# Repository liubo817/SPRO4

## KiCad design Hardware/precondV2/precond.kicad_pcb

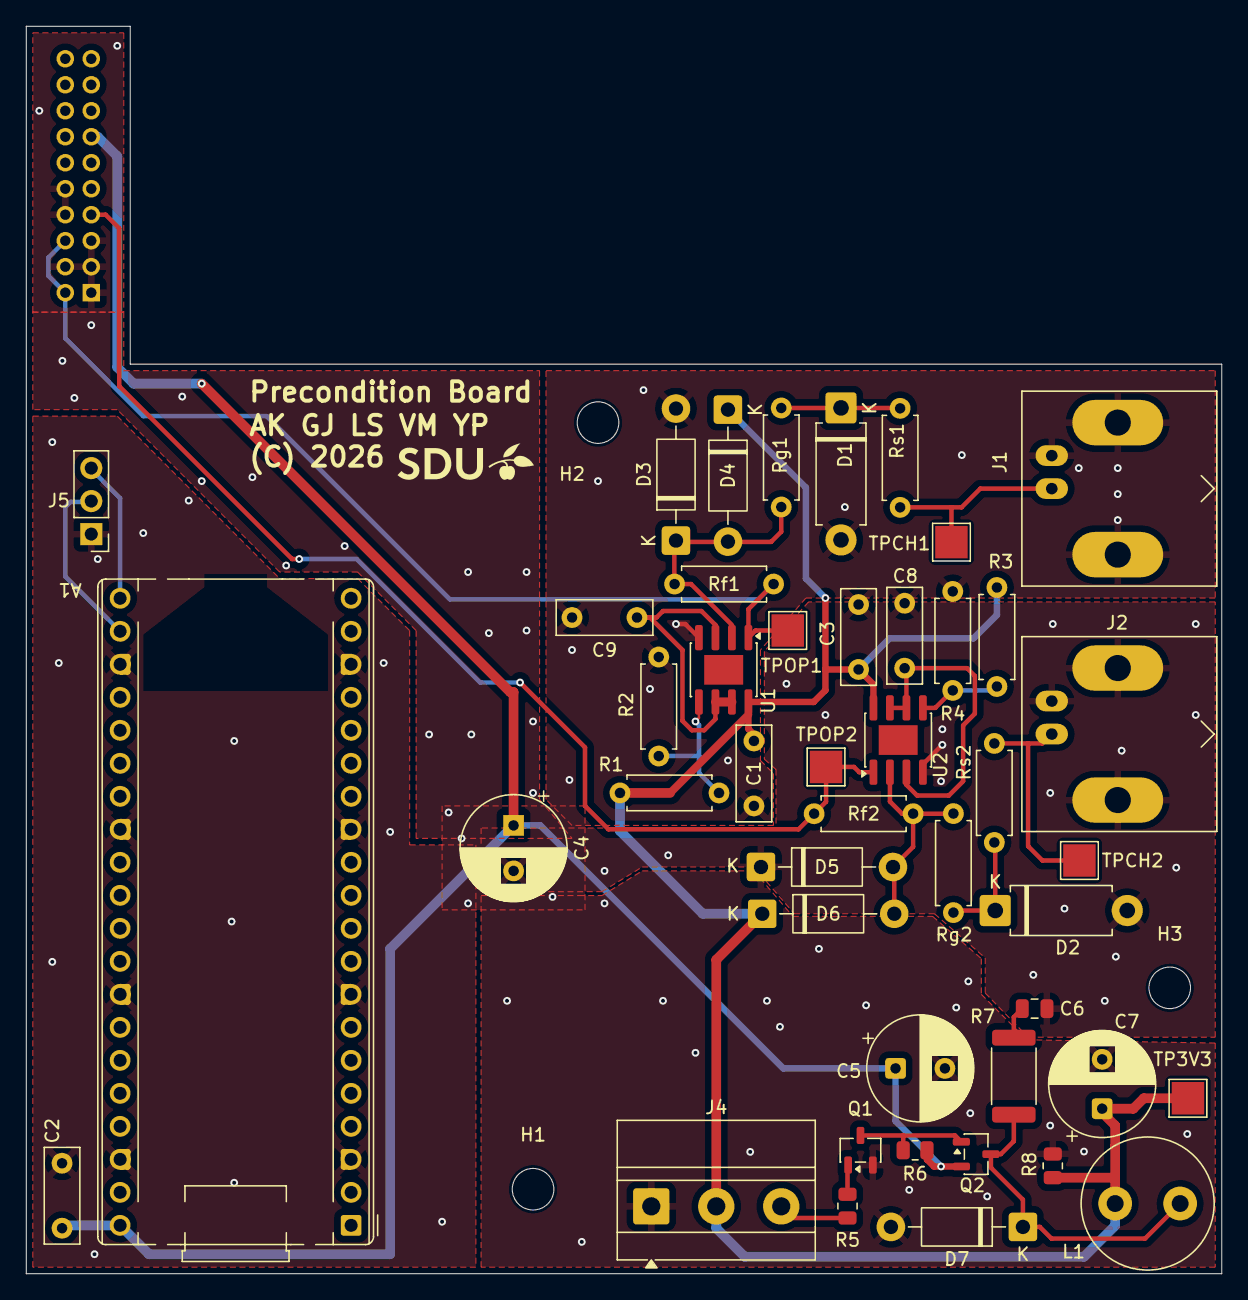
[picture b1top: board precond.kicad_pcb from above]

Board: 2 copper layers, 92.0 x 96.0 mm, 49 parts (1 on the bottom side), 22 nets.

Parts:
A1: RaspberryPi_Pico; RaspberryPi_Pico_Common_THT
C1, C2, C3, C8, C9: 100n; C_Rect_L7.2mm_W2.5mm_P5.00mm_FKS2_FKP2_MKS2_MKP2
C4: 47uF; CP_Radial_D8.0mm_P3.50mm
C5: 100uF; CP_Radial_D8.0mm_P3.80mm
C6: 1n; C_0805_2012Metric
C7: 220uF; CP_Radial_D8.0mm_P3.80mm
D1, D2: P6KE18CA; D_DO-15_P10.16mm_Horizontal
D3, D4, D5, D6, D7: 1N5819; D_DO-41_SOD81_P10.16mm_Horizontal
H1, H2, H3: MountingHole; MountingHole_3.2mm_M3
J1, J2: Conn_Coaxial; BNC_Amphenol_B6252HB-NPP3G-50_Horizontal
J3: XADC_header; PinSocket_2x10_P2.00mm_Vertical
J4: Screw_Terminal_01x03; TerminalBlock_MetzConnect_Type011_RT05503HBLC_1x03_P5.00mm_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
J5: UART_hdr; PinHeader_1x03_P2.54mm_Vertical
L1: 470uH; L_Radial_D10.0mm_P5.00mm_Fastron_07M
Q1: IRLML6344TRPBF; SOT-23-3
Q2: IRLML9301TRPBF; SOT-23-3
R1, R3: 56k; R_Axial_DIN0207_L6.3mm_D2.5mm_P7.62mm_Horizontal
R2, R4: 10k; R_Axial_DIN0207_L6.3mm_D2.5mm_P7.62mm_Horizontal
R5, R8: 1k; R_0805_2012Metric
R6: 100; R_0805_2012Metric
R7: 22; R_2512_6332Metric
Rf1, Rf2: 200k; R_Axial_DIN0207_L6.3mm_D2.5mm_P7.62mm_Horizontal
Rg1, Rg2: 200k; R_Axial_DIN0207_L6.3mm_D2.5mm_P7.62mm_Horizontal
Rs1, Rs2: 1k; R_Axial_DIN0207_L6.3mm_D2.5mm_P7.62mm_Horizontal
TP3V3: TestPoint; TestPoint_Pad_2.5x2.5mm
TPCH1, TPCH2: TestPoint; TestPoint_Pad_2.5x2.5mm
TPOP1, TPOP2: TestPoint; TestPoint_Pad_2.5x2.5mm
U1, U2: OPA2340; SOIC-8-1EP_3.9x4.9mm_P1.27mm_EP2.29x3mm

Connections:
+3.3V: C1.1, C3.1, C7.1, D4.1 (K), D6.1 (K), J4.2, L1.2, R1.1, R3.1, R8.1, TP3V3.1, U1.8 (V+), U2.8 (V+)
+5V: A1.40 (VBUS), C2.2, C4.1, C5.1, J3.13, Q2.2, R6.1
/Op0.5V_1: C9.1, U1.3 (+), U1.6 (-), U1.7
/Op0.5_2: C8.1, U2.3 (+), U2.6 (-), U2.7
/Op1_out: J3.2, J3.6, Rf1.2, TPOP1.1, U1.1
/Op2_out: J3.7, Rf2.2, TPOP2.1, U2.1
AGND: A1.3 (GND), A1.8 (GND), A1.13 (GND), A1.18 (GND), A1.23 (GND), A1.28 (GND), A1.33 (AGND), A1.38 (GND), C1.2, C2.1, C3.2, C4.2, C5.2, C6.2, C7.2, C8.2, C9.2, D1.2 (A2), D2.2 (A2), D3.2 (A), D5.1 (K), D7.2 (A), J1.2 (Ext), J2.2 (Ext), J3.1, J3.3, J3.4, J3.5, J3.8, J3.10, J4.1, J5.1, Q1.2, R2.2, R4.2, R8.2, U1.4 (V-), U2.4 (V-)
unnamed: A1.21 (GPIO16), J5.3
unnamed: A1.22 (GPIO17), J5.2
unnamed: C6.1, R7.2
unnamed: D1.1 (A1), Rg1.1, Rs1.2
unnamed: D2.1 (A1), Rg2.1, Rs2.2
unnamed: D3.1 (K), D4.2 (A), Rf1.1, Rg1.2, U1.2 (-)
unnamed: D5.2 (A), D6.2 (A), Rf2.1, Rg2.2, U2.2 (-)
unnamed: D7.1 (K), L1.1, Q2.3, R7.1
unnamed: J1.1 (In), Rs1.1, TPCH1.1
unnamed: J2.1 (In), Rs2.1, TPCH2.1
unnamed: J4.3, R5.2
unnamed: Q1.1, R5.1
unnamed: Q1.3, Q2.1, R6.2
unnamed: R1.2, R2.1, U1.5 (+)
unnamed: R3.2, R4.1, U2.5 (+)

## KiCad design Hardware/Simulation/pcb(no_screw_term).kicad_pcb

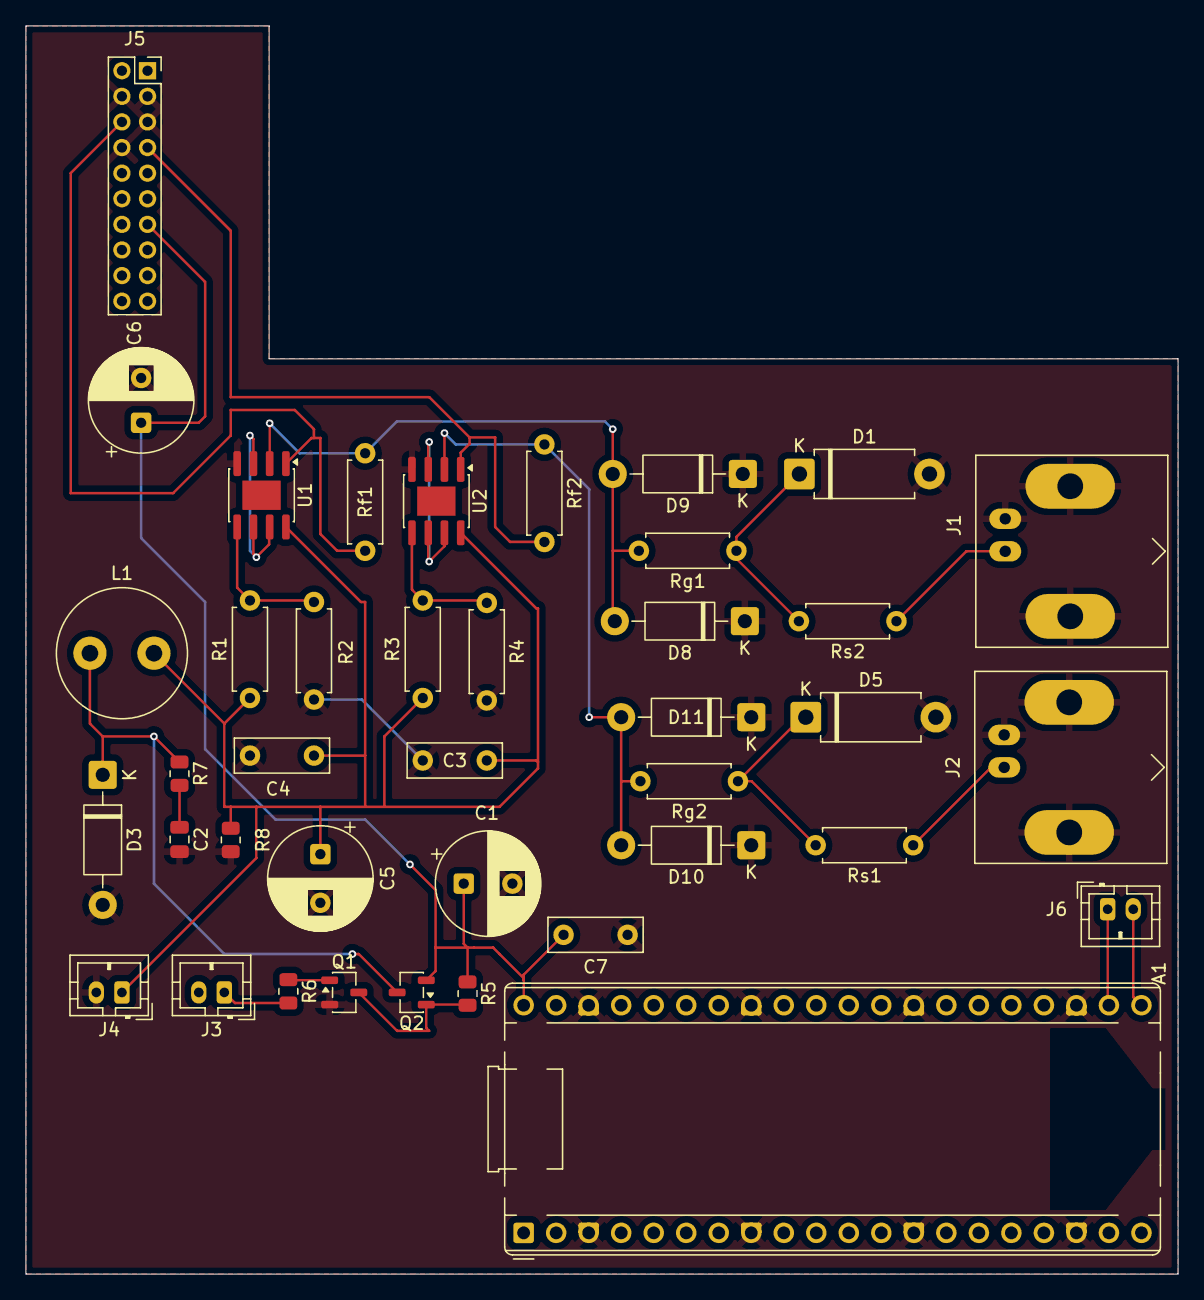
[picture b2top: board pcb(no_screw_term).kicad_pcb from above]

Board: 2 copper layers, 90.0 x 97.5 mm, 40 parts (0 on the bottom side), 22 nets.

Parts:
A1: RaspberryPi_Pico; RaspberryPi_Pico_Common_THT
C1: 100uF; CP_Radial_D8.0mm_P3.80mm
C2: 1n; C_0805_2012Metric
C3, C4, C7: 100n; C_Rect_L7.2mm_W2.5mm_P5.00mm_FKS2_FKP2_MKS2_MKP2
C5: 220uF; CP_Radial_D8.0mm_P3.80mm
C6: 47uF; CP_Radial_D8.0mm_P3.50mm
D1, D5: P6KE18CA; D_DO-15_P10.16mm_Horizontal
D3, D8, D9, D10, D11: 1N5819; D_DO-41_SOD81_P10.16mm_Horizontal
J1, J2: Conn_Coaxial; BNC_Amphenol_B6252HB-NPP3G-50_Horizontal
J3: Buck_logic_in; JST_PH_B2B-PH-K_1x02_P2.00mm_Vertical
J4: 3.3V_header; JST_PH_B2B-PH-K_1x02_P2.00mm_Vertical
J5: XADC_headder; PinSocket_2x10_P2.00mm_Vertical
J6: Pmod_to_UART; JST_PH_B2B-PH-K_1x02_P2.00mm_Vertical
L1: 470uH; L_Radial_D10.0mm_P5.00mm_Fastron_07M
Q1: IRLML6344TRPBF; SOT-23-3
Q2: IRLML9301TRPBF; SOT-23-3
R1, R3: 56k; R_Axial_DIN0207_L6.3mm_D2.5mm_P7.62mm_Horizontal
R2, R4: 10k; R_Axial_DIN0207_L6.3mm_D2.5mm_P7.62mm_Horizontal
R5: 100; R_0805_2012Metric
R6, R8: 1k; R_0805_2012Metric
R7: 22; R_0805_2012Metric
Rf1, Rf2: 200k; R_Axial_DIN0207_L6.3mm_D2.5mm_P7.62mm_Horizontal
Rg1, Rg2: 200k; R_Axial_DIN0207_L6.3mm_D2.5mm_P7.62mm_Horizontal
Rs1, Rs2: 1k; R_Axial_DIN0207_L6.3mm_D2.5mm_P7.62mm_Horizontal
U1, U2: OPA2340; SOIC-8-1EP_3.9x4.9mm_P1.27mm_EP2.29x3mm

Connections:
+3.3V: C3.1, C4.1, C5.1, J4.1, L1.2, R1.1, R3.1, R8.1, U1.8 (V+), U2.8 (V+)
+5V: A1.40 (VBUS), C1.1, C6.1, C7.2, J5.13, Q2.2, R5.1
/Op0.5V_1: U1.3 (+), U1.6 (-), U1.7
/Op0.5_2: U2.3 (+), U2.6 (-), U2.7
/Op1_out: J5.6, Rf1.2, U1.1
/Op2_out: J5.7, Rf2.2, U2.1
GND: A1.3 (GND), A1.8 (GND), A1.13 (GND), A1.18 (GND), A1.23 (GND), A1.28 (GND), A1.33 (AGND), A1.38 (GND), C1.2, C2.2, C3.2, C4.2, C5.2, C6.2, C7.1, D1.2 (A2), D3.2 (A), D5.2 (A2), D8.1 (K), D9.1 (K), D10.1 (K), D11.1 (K), J1.2 (Ext), J2.2 (Ext), J4.2, J5.3, J5.4, J5.5, J5.8, Q1.2, R2.2, R4.2, R8.2, U1.4 (V-), U2.4 (V-)
unnamed: A1.21 (GPIO16), J6.2
unnamed: A1.22 (GPIO17), J6.1
unnamed: C2.1, R7.2
unnamed: D1.1 (A1), Rg1.1, Rs2.2
unnamed: D3.1 (K), L1.1, Q2.3, R7.1
unnamed: D5.1 (A1), Rg2.1, Rs1.2
unnamed: D8.2 (A), D9.2 (A), Rf1.1, Rg1.2, U1.2 (-)
unnamed: D10.2 (A), D11.2 (A), Rf2.1, Rg2.2, U2.2 (-)
unnamed: J1.1 (In), Rs2.1
unnamed: J2.1 (In), Rs1.1
unnamed: J3.1, R6.2
unnamed: Q1.1, R6.1
unnamed: Q1.3, Q2.1, R5.2
unnamed: R1.2, R2.1, U1.5 (+)
unnamed: R3.2, R4.1, U2.5 (+)

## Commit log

2026-03-30 testing (write bitstream error)
2026-03-30 testing - w11 pin doesnt output pwm, but everything compiles
2026-03-30 testing - PWM output is working but its not changing as adc changes
2026-04-01 uart thing that probably doesn't work lol
2026-04-05 UART module works with testbench
2026-04-11 precondition pcb part 1
2026-04-11 scheme
2026-04-11 precondition pcb V02
2026-04-11 bullshit
2026-04-11 cleanup
2026-04-11 cleanup2
2026-04-11 Precondition cleanup
2026-04-12 Added the python file
2026-04-15 Power elec laid down, 20vpp max added
2026-04-16 UART and Wave generation should be done, hopefully
2026-04-17 buck
    buck
2026-04-17 precond simulation finished
2026-04-17 uart generation
2026-04-17 precondition sim
2026-04-17 simualtion
2026-04-18 started restructuring code to accommodate for internal trigger, made decimator
2026-04-19 connect stuff. need to add code for RX next
2026-04-20 mild tweak, not finished
2026-04-24 func gen pwm trust
2026-04-24 func gen done
2026-04-26 precondition circuit redesign
2026-04-27 changes to op-amp PCB. needs footprints!
2026-04-27 stuff
2026-04-27 stuff 2
2026-05-03 might work, might not, but here is some UART code (w trigger skipped)
2026-05-03 wip commit
2026-05-03 for adam
2026-05-04 kill me
2026-05-04 doo doo ass
2026-05-04 update schematic with new transistors
2026-05-05 footprints and stuff
2026-05-05 fixed ams conn trust
2026-05-05 adam plz make pcb
2026-05-05 Revert "adam plz make pcb"
    This reverts commit e55343ee625ea9e67b9447f2fa8b2d599a8bbbfe.
2026-05-05 adam make pcb
2026-05-05 bug fix
2026-05-08 PCB design added
    The PCB design ha been added to the precondition file
2026-05-08 PCB schematic changes
2026-05-09 pcb with ground plane + minor fixes
2026-05-09 pcb backup upload
2026-05-09 yanis do the thing you wanted i left the header and microcontroller for you on top
2026-05-11 finished?
2026-05-11 Maybe the VHDL is done, needs testing
2026-05-12 asdf
2026-05-13 Another version of the PCB
2026-05-13 V2 of the PCB
2026-05-13 Fabrication files
2026-05-13 added platform MHs
2026-05-13 final pcb
2026-05-17 cleanup + hw trigger?
2026-05-17 readded old stuff
2026-05-22 alright
2026-05-22 python app fixes
2026-05-22 fixed decimator
2026-05-25 mrow
2026-05-26 nlewjgjgao
2026-05-26 app is trustworthy, no button for edge tho
2026-05-26 nhjagjisghjdhjhnkl
2026-05-28 app finished, all buttons + clearer UI
2026-05-28 func gen fixes of duty cycle + constraints
2026-05-28 vhdl cleanup
2026-05-29 cleanup 2
2026-05-29 more stuff
2026-05-29 cleaning of the python app + dimensions of the pcb
2026-05-31 fix stuff
2026-05-31 itty bitty var rename
2026-06-01 remove some useless comments
2026-06-16 removed some comments, changed D to 66 on buckpwm
2026-06-16 fixed precond simul ltspice voltage
2026-06-16 simulation fixed

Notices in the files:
Hardware/precondV2/precond.kicad_pcb:
(C) 2026
